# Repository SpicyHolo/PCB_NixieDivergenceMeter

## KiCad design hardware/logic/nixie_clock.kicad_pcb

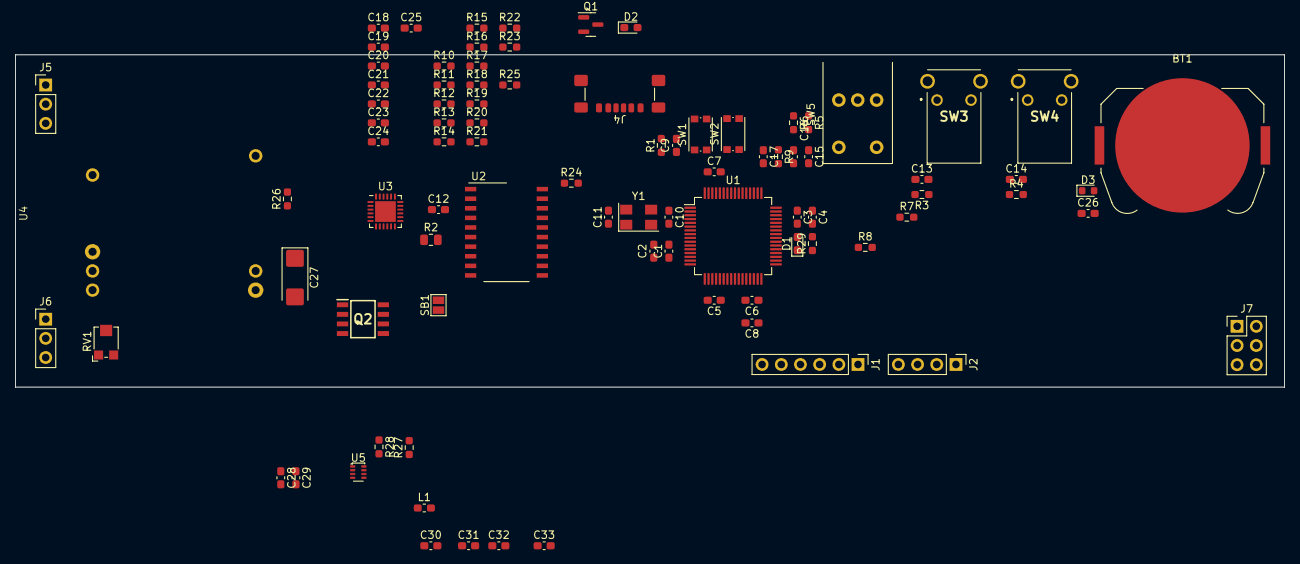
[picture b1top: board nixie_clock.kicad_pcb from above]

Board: 2 copper layers, 168.0 x 44.0 mm, 88 parts (0 on the bottom side), 56 nets.

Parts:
BT1: CR2032; BatteryHolder_Keystone_3034_1x20mm
C1: 10 nF; C_0603_1608Metric_Pad1.08x0.95mm_HandSolder
C2: 1 uF; C_0603_1608Metric_Pad1.08x0.95mm_HandSolder
C3, C5, C6, C7, C9, C12, C26: 100 nF; C_0603_1608Metric_Pad1.08x0.95mm_HandSolder
C4, C8: 4.7 uF; C_0603_1608Metric_Pad1.08x0.95mm_HandSolder
C10, C11: 10p; C_0603_1608Metric_Pad1.08x0.95mm_HandSolder
C13, C14, C17: 1u; C_0603_1608Metric_Pad1.08x0.95mm_HandSolder
C15, C16: 10n; C_0603_1608Metric_Pad1.08x0.95mm_HandSolder
C18, C22, C23, C25: 4u7; C_0603_1608Metric_Pad1.08x0.95mm_HandSolder
C19, C20, C21, C24, C29, C31: 100n; C_0603_1608Metric_Pad1.08x0.95mm_HandSolder
C27: 10uF; CP_EIA-6032-15_Kemet-U_Pad2.25x2.35mm_HandSolder
C28: 10u; C_0603_1608Metric_Pad1.08x0.95mm_HandSolder
C30: 33n; C_0603_1608Metric_Pad1.08x0.95mm_HandSolder
C32: 22p; C_0603_1608Metric_Pad1.08x0.95mm_HandSolder
C33: 100u; C_0603_1608Metric_Pad1.08x0.95mm_HandSolder
D1, D2: LED; LED_0603_1608Metric_Pad1.05x0.95mm_HandSolder
D3: BAT64-02V; D_0603_1608Metric
J1: Conn_01x06_Pin; PinHeader_1x06_P2.54mm_Vertical
J2: Conn_01x04; PinHeader_1x04_P2.54mm_Vertical
J4: USB_C_PD; USB_C_Receptacle_GCT_USB4135-GF-A_6P_TopMnt_Horizontal
J5, J6: Conn_01x03; PinHeader_1x03_P2.54mm_Vertical
J7: Conn_02x03_Odd_Even; PinHeader_2x03_P2.54mm_Vertical
L1: 5.6uH; L_0603_1608Metric_Pad1.05x0.95mm_HandSolder
Q1: 2N7002NXAKR; SOT-23
Q2: DMP3098LSD-13; SOIC127P600X175-8N
R1: 10K; R_0603_1608Metric_Pad0.98x0.95mm_HandSolder
R2: 10K; R_0805_2012Metric
R3, R4, R5, R6, R7, R8, R9, R28: 10k; R_0603_1608Metric_Pad0.98x0.95mm_HandSolder
R10, R11, R12, R13, R19, R20, R22, R23, R24, R29: 2k2; R_0603_1608Metric_Pad0.98x0.95mm_HandSolder
R14, R25: 20k; R_0603_1608Metric_Pad0.98x0.95mm_HandSolder
R15, R17: 5k1; R_0603_1608Metric_Pad0.98x0.95mm_HandSolder
R16, R18: 2k4; R_0603_1608Metric_Pad0.98x0.95mm_HandSolder
R21: DNP; R_0603_1608Metric_Pad0.98x0.95mm_HandSolder
R26: 100k; R_0603_1608Metric_Pad0.98x0.95mm_HandSolder
R27: 30k9; R_0603_1608Metric_Pad0.98x0.95mm_HandSolder
RV1: 100k; Potentiometer_Bourns_TC33X_Vertical
SB1: GS2; SolderJumper-2_P1.3mm_Open_Pad1.0x1.5mm
SW1: SW_RST; SW_Push_1P1T_NO_CK_KMR2
SW2: SW_BOOT; SW_Push_1P1T_NO_CK_KMR2
SW3, SW4: FSMRA4JH04
SW5: RotaryEncoder_Switch; RotaryEncoder_Bourns_Horizontal_PEC09-2xxxF-Sxxxx
U1: STM32F072RBTx; LQFP-64_10x10mm_P0.5mm
U2: DS3234; SO-20_12.8x7.5mm_P1.27mm
U3: CYPD3177-24LQXQ; QFN-24-1EP_4x4mm_P0.5mm_EP2.75x2.75mm
U4: 1364 HVPS; 1364 HVPS horizontal
U5: TPS62933FDRL; SOT-583-8
Y1: 8 MHz; Crystal_SMD_5032-4Pin_5.0x3.2mm

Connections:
+3.3V: C1.1, C2.1, C3.1, C4.1, C5.1, C6.1, C7.1, C8.1, C20.1, C21.1, C22.1, C32.1, C33.1, D2.2 (A), J1.1, J2.1, L1.2, R10.1, R11.1, R12.1, R15.1, R17.1, R19.1, R21.1, R27.1, U1.13 (VDDA), U1.19 (VDD), U1.32 (VDD), U1.48 (VDDIO2), U1.64 (VDD), U3.23 (VDDD)
+3V3: C12.1, J7.2, R2.2, R5.1, R6.1, SW2.2, SW3.2 (NO), SW4.2 (NO), SW5.S1, U2.4 (VCC)
+12V: C24.1, J7.1, Q2.5 (D2_1), Q2.6 (D2_2), U3.11 (VDC_OUT)
+BATT: C26.1, D3.1 (K), U1.1 (VBAT), U2.16 (VBAT)
+HV: J5.1, J5.2, J5.3, U4.1 (Vout)
/nixie_clock-MCU/BLANK: J7.3, U1.41 (PA8)
/nixie_clock-MCU/BOOT0: R1.2, SW2.1, U1.60 (BOOT0)
/nixie_clock-MCU/DEV_LED_K: D1.1 (K), R29.1
/nixie_clock-MCU/ENC_A: C15.1, R7.1, U1.14 (PA0)
/nixie_clock-MCU/ENC_B: C16.1, R8.1, U1.15 (PA1)
/nixie_clock-MCU/ENC_SW: C17.1, R9.1, SW5.S2, U1.16 (PA2)
/nixie_clock-MCU/HSE_IN: C10.1, U1.5 (PF0), Y1.3
/nixie_clock-MCU/HSE_OUT: C11.1, U1.6 (PF1), Y1.1
/nixie_clock-MCU/HVPS_EN: R26.2, U1.61 (PB8), U4.7 (Enable)
/nixie_clock-MCU/I2C1_SCL: R11.2, U1.58 (PB6), U3.13 (HPI_SCL)
/nixie_clock-MCU/I2C1_SDA: R12.2, U1.59 (PB7), U3.12 (HPI_SDA)
/nixie_clock-MCU/PD_FLIP: R10.2, U1.57 (PB5), U3.10 (FLIP)
/nixie_clock-MCU/RXD: J2.4, U1.42 (PA9)
/nixie_clock-MCU/SP1_NSS_DISP: J7.5, U1.51 (PC10)
/nixie_clock-MCU/SP1_NSS_RTC: U1.52 (PC11), U2.1 (~CS)
/nixie_clock-MCU/SP1_SCK: J7.6, U1.21 (PA5), U2.18 (SCK), U2.20 (SCK)
/nixie_clock-MCU/SPI1_MISO: U1.22 (PA6), U2.19 (DOUT)
/nixie_clock-MCU/SPI1_MOSI: J7.4, U1.23 (PA7), U2.17 (DIN)
/nixie_clock-MCU/SQW_IN: R2.1, U1.2 (PC13), U2.5 (~INT/SQW)
/nixie_clock-MCU/SW1: C13.1, R3.2, SW3.1 (COM), U1.17 (PA3)
/nixie_clock-MCU/SW2: C14.1, R4.2, SW4.1 (COM), U1.20 (PA4)
/nixie_clock-MCU/SWCLK: J1.2, U1.49 (PA14)
/nixie_clock-MCU/SWDIO: J1.4, U1.46 (PA13)
/nixie_clock-MCU/SW_RST: C9.1, J1.5, SB1.1 (G1), SW1.2, U1.7 (NRST)
/nixie_clock-MCU/TXD: J2.3, U1.43 (PA10)
/nixie_clock-PSU/FET_FAULT_D: Q1.3 (D), R13.2
/nixie_clock-PSU/LED_FAULT_K: D2.1 (K), R13.1
/nixie_clock-PSU/PDC_VCCD: C23.1, U3.24 (VCCD)
/nixie_clock-PSU/VBUS_FET_EN: R23.2, U3.3 (VBUS_FET_EN)
/nixie_clock-PSU/VBUS_FET_EN_R: C24.2, C25.2, R23.1, R24.2, R25.1
/nixie_clock-PSU/VBUS_FET_G: Q2.1 (S1), Q2.2 (G1), Q2.3 (S2), Q2.4 (G2), R24.1
GND: BT1.2 (-), C1.2, C2.2, C3.2, C4.2, C5.2, C6.2, C7.2, C8.2, C9.2, C10.2, C11.2, C12.2, C13.2, C14.2, C15.2, C16.2, C17.2, C18.2, C19.2, C20.2, C21.2, C22.2, C23.2, C26.2, C27.2, C28.2, C29.2, C30.2, C33.2, J1.3, J2.2, J4.A12 (GND), J4.B12 (GND), J4.S1 (SHIELD), J6.1, J6.2, J6.3, Q1.2 (S), R1.1, R3.1, R4.1, R9.2, R14.1, R16.2, R18.2, R20.2, R22.2, R26.1, R28.2, R29.2, RV1.3, SW1.1, SW3.3 (MH1), SW3.4 (MH2), SW4.3 (MH1), SW4.4 (MH2), SW5.C, U1.12 (VSSA), U1.18 (VSS), U1.31 (VSS), U1.47 (VSS), U1.63 (VSS), U2.2 (NC(CTG)), U2.7 (NC(CTG)), U2.8 (NC(CTG)), U2.9 (NC(CTG)), U2.10 (NC(CTG)), U2.11 (NC(CTG)), U2.12 (NC(CTG)), U2.13 (NC(CTG)), U2.14 (NC(CTG)), U2.15 (GND), U3.19 (GND), U3.22 (GND), U3.25 (GND), U4.3 (Gnd), U4.5 (Gnd), U5.4 (GND), Y1.2, Y1.4
unnamed: BT1.1 (+), D3.2 (A)
unnamed: D1.2 (A), U1.44 (PA11)
unnamed: J4.A5 (CC1), U3.15 (CC1)
unnamed: J4.B5 (CC2), U3.14 (CC2)
unnamed: Q1.1 (G), R14.2, U3.9 (FAULT)
unnamed: R5.2, R8.2, SW5.B
unnamed: R6.2, R7.2, SW5.A
unnamed: SB1.2 (G2), U2.6 (~RST)
unnamed: R19.2, R20.1, U3.5 (ISNK_COARSE)
unnamed: R21.2, R22.1, U3.6 (ISNK_FINE)
unnamed: R15.2, R16.1, U3.2 (VBUS_MAX)
unnamed: R17.2, R18.1, U3.1 (VBUS_MIN)
unnamed: RV1.2, U4.2 (Radj)
unnamed: C27.1, U4.4 (Vin)
unnamed: C31.1, U5.6 (BST)
unnamed: C32.2, R27.2, R28.1, U5.8 (FB)
unnamed: C30.1, U5.7 (SS)
unnamed: C31.2, L1.1, U5.5 (SW)
VBUS: C18.1, C19.1, C25.1, C28.1, C29.1, J4.A9 (VBUS), J4.B9 (VBUS), Q2.7 (D1_1), Q2.8 (D1_2), R25.2, U3.18 (VBUS_IN), U5.3 (VIN)

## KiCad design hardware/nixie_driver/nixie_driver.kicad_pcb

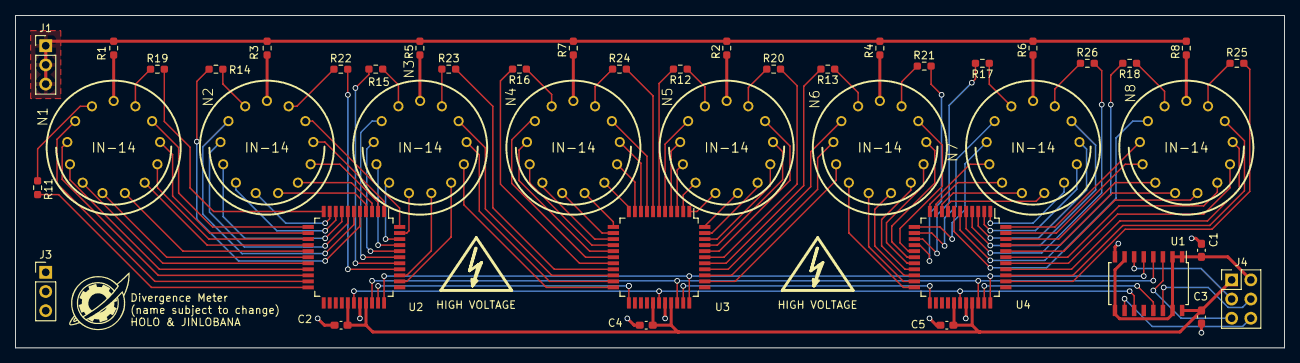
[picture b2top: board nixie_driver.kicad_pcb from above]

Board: 2 copper layers, 168.0 x 44.0 mm, 45 parts (0 on the bottom side), 134 nets.

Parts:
C1, C2, C3, C4, C5: 100nF; C_0603_1608Metric_Pad1.08x0.95mm_HandSolder
IMG1: LOGO; future_gadget_lab_neg_tiny
J1, J3: Conn_01x03; PinHeader_1x03_P2.54mm_Vertical
J4: Conn_02x03_Odd_Even; PinHeader_2x03_P2.54mm_Vertical
N1, N2, N3, N4, N5, N6, N7, N8: IN-14; nixies-us-IN-14
R1, R2, R3, R4, R5, R6, R7, R8: 10k; R_0603_1608Metric_Pad0.98x0.95mm_HandSolder
R11, R12, R13, R14, R15, R16, R17, R18, R19, R20, R21, R22, R23, R24, R25, R26: 73k; R_0603_1608Metric_Pad0.98x0.95mm_HandSolder
U1: CD40109B; SOIC-16W_5.3x10.2mm_P1.27mm
U2, U3, U4: TubeClock_HV5622; PQFP-44_10x10mm_P0.8mm

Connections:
+3.3V: C1.1, J4.2, U1.1 (VCC), U1.2 (ENABLE_A), U1.7 (ENABLE_B), U1.9 (ENABLE_C), U1.15 (ENABLE_D)
+12V: C2.1, C3.1, C4.1, C5.1, J4.1, U1.16 (VDD), U2.27 (~POL), U2.30 (VDD), U3.27 (~POL), U3.30 (VDD), U4.27 (~POL), U4.30 (VDD)
+HV: J1.1, J1.2, J1.3, R1.2, R2.2, R3.2, R4.2, R5.2, R6.2, R7.2, R8.2
/CLK: U1.11 (OUTPUT_C), U2.28 (CLK), U3.28 (CLK), U4.28 (CLK)
/CLK_{3.3V}: J4.6, U1.10 (INPUT_C)
/D_{IN}: U1.13 (OUTPUT_D), U4.32 (DATA_IN)
/D_{IN}_{3.3V}: J4.4, U1.14 (INPUT_D)
/D_{OUT1}: U3.32 (DATA_IN), U4.23 (DATA_OUT)
/D_{OUT2}: U2.32 (DATA_IN), U3.23 (DATA_OUT)
/NX1_K0: N1.0, U2.12 (HVOUT11)
/NX1_K1: N1.1, U2.21 (HVOUT2)
/NX1_K2: N1.2, U2.20 (HVOUT3)
/NX1_K3: N1.3, U2.19 (HVOUT4)
/NX1_K4: N1.4, U2.18 (HVOUT5)
/NX1_K5: N1.5, U2.17 (HVOUT6)
/NX1_K6: N1.6, U2.16 (HVOUT7)
/NX1_K7: N1.7, U2.15 (HVOUT8)
/NX1_K8: N1.8, U2.14 (HVOUT9)
/NX1_K9: N1.9, U2.13 (HVOUT10)
/NX1_LP: R11.2, U2.22 (HVOUT1)
/NX1_RP: R19.2, U2.11 (HVOUT12)
/NX2_K0: N2.0, U2.44 (HVOUT23)
/NX2_K1: N2.1, U2.6 (HVOUT17)
/NX2_K2: N2.2, U2.7 (HVOUT16)
/NX2_K3: N2.3, U2.8 (HVOUT15)
/NX2_K4: N2.4, U2.9 (HVOUT14)
/NX2_K5: N2.5, U2.10 (HVOUT13)
/NX2_K6: N2.6, U2.4 (HVOUT19)
/NX2_K7: N2.7, U2.3 (HVOUT20)
/NX2_K8: N2.8, U2.2 (HVOUT21)
/NX2_K9: N2.9, U2.1 (HVOUT22)
/NX2_LP: R14.2, U2.5 (HVOUT18)
/NX2_RP: R22.2, U2.37 (HVOUT30)
/NX3_K0: N3.0, U3.20 (HVOUT3)
/NX3_K1: N3.1, U2.39 (HVOUT28)
/NX3_K2: N3.2, U2.40 (HVOUT27)
/NX3_K3: N3.3, U2.41 (HVOUT26)
/NX3_K4: N3.4, U2.42 (HVOUT25)
/NX3_K5: N3.5, U2.43 (HVOUT24)
/NX3_K6: N3.6, U2.36 (HVOUT31)
/NX3_K7: N3.7, U2.35 (HVOUT32)
/NX3_K8: N3.8, U3.22 (HVOUT1)
/NX3_K9: N3.9, U3.21 (HVOUT2)
/NX3_LP: R15.2, U2.38 (HVOUT29)
/NX3_RP: R23.2, U3.19 (HVOUT4)
/NX4_K0: N4.0, U3.8 (HVOUT15)
/NX4_K1: N4.1, U3.17 (HVOUT6)
/NX4_K2: N4.2, U3.16 (HVOUT7)
/NX4_K3: N4.3, U3.15 (HVOUT8)
/NX4_K4: N4.4, U3.14 (HVOUT9)
/NX4_K5: N4.5, U3.13 (HVOUT10)
/NX4_K6: N4.6, U3.12 (HVOUT11)
/NX4_K7: N4.7, U3.11 (HVOUT12)
/NX4_K8: N4.8, U3.10 (HVOUT13)
/NX4_K9: N4.9, U3.9 (HVOUT14)
/NX4_LP: R16.2, U3.18 (HVOUT5)
/NX4_RP: R24.2, U3.7 (HVOUT16)
/NX5_K0: N5.0, U3.40 (HVOUT27)
/NX5_K1: N5.1, U3.5 (HVOUT18)
/NX5_K2: N5.2, U3.4 (HVOUT19)
/NX5_K3: N5.3, U3.3 (HVOUT20)
/NX5_K4: N5.4, U3.2 (HVOUT21)
/NX5_K5: N5.5, U3.1 (HVOUT22)
/NX5_K6: N5.6, U3.44 (HVOUT23)
/NX5_K7: N5.7, U3.43 (HVOUT24)
/NX5_K8: N5.8, U3.42 (HVOUT25)
/NX5_K9: N5.9, U3.41 (HVOUT26)
/NX5_LP: R12.2, U3.6 (HVOUT17)
/NX5_RP: R20.2, U3.39 (HVOUT28)
/NX6_K0: N6.0, U4.16 (HVOUT7)
/NX6_K1: N6.1, U3.37 (HVOUT30)
/NX6_K2: N6.2, U3.36 (HVOUT31)
/NX6_K3: N6.3, U3.35 (HVOUT32)
/NX6_K4: N6.4, U4.22 (HVOUT1)
/NX6_K5: N6.5, U4.21 (HVOUT2)
/NX6_K6: N6.6, U4.20 (HVOUT3)
/NX6_K7: N6.7, U4.19 (HVOUT4)
/NX6_K8: N6.8, U4.18 (HVOUT5)
/NX6_K9: N6.9, U4.17 (HVOUT6)
/NX6_LP: R13.2, U3.38 (HVOUT29)
/NX6_RP: R21.2, U4.15 (HVOUT8)
/NX7_K0: N7.0, U4.4 (HVOUT19)
/NX7_K1: N7.1, U4.13 (HVOUT10)
/NX7_K2: N7.2, U4.12 (HVOUT11)
/NX7_K3: N7.3, U4.11 (HVOUT12)
/NX7_K4: N7.4, U4.10 (HVOUT13)
/NX7_K5: N7.5, U4.9 (HVOUT14)
/NX7_K6: N7.6, U4.8 (HVOUT15)
/NX7_K7: N7.7, U4.1 (HVOUT22)
/NX7_K8: N7.8, U4.2 (HVOUT21)
/NX7_K9: N7.9, U4.3 (HVOUT20)
/NX7_LP: R17.2, U4.14 (HVOUT9)
/NX7_RP: R26.2, U4.5 (HVOUT18)
/NX8_K0: N8.0, U4.36 (HVOUT31)
/NX8_K1: N8.1, U4.7 (HVOUT16)
/NX8_K2: N8.2, U4.44 (HVOUT23)
/NX8_K3: N8.3, U4.43 (HVOUT24)
/NX8_K4: N8.4, U4.42 (HVOUT25)
/NX8_K5: N8.5, U4.41 (HVOUT26)
/NX8_K6: N8.6, U4.40 (HVOUT27)
/NX8_K7: N8.7, U4.39 (HVOUT28)
/NX8_K8: N8.8, U4.38 (HVOUT29)
/NX8_K9: N8.9, U4.37 (HVOUT30)
/NX8_LP: R18.2, U4.6 (HVOUT17)
/NX8_RP: R25.2, U4.35 (HVOUT32)
/~BL: U1.5 (OUTPUT_B), U2.33 (~BL), U3.33 (~BL), U4.33 (~BL)
/~BL_{3.3V}: J4.3, U1.6 (INPUT_B)
/~LE: U1.4 (OUTPUT_A), U2.31 (~LE), U3.31 (~LE), U4.31 (~LE)
/~LE_{3.3V}: J4.5, U1.3 (INPUT_A)
GND: C1.2, C2.2, C3.2, C4.2, C5.2, J3.1, J3.2, J3.3, U1.8 (VSS), U2.29 (VSS), U3.29 (VSS), U4.29 (VSS)
unnamed: N1.A, R1.1
unnamed: N1.LHDP, R11.1
unnamed: N1.RHDP, R19.1
unnamed: N2.A, R3.1
unnamed: N2.LHDP, R14.1
unnamed: N2.RHDP, R22.1
unnamed: N3.A, R5.1
unnamed: N3.LHDP, R15.1
unnamed: N3.RHDP, R23.1
unnamed: N4.A, R7.1
unnamed: N4.LHDP, R16.1
unnamed: N4.RHDP, R24.1
unnamed: N5.A, R2.1
unnamed: N5.LHDP, R12.1
unnamed: N5.RHDP, R20.1
unnamed: N6.A, R4.1
unnamed: N6.LHDP, R13.1
unnamed: N6.RHDP, R21.1
unnamed: N7.A, R6.1
unnamed: N7.LHDP, R17.1
unnamed: N7.RHDP, R26.1
unnamed: N8.A, R8.1
unnamed: N8.LHDP, R18.1
unnamed: N8.RHDP, R25.1

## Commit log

2023-11-15 Init repo
2023-11-17 Re-init
2023-12-04 Rough version of Main and driver board
2023-12-04 Changed connectors to driver board, fixed oscillator connections
2023-12-04 Inital PCB placement
2023-12-30 PCB layout, traces for nixie_driver, 3 Nixies + logic
2023-12-30 Finish PCB design for nixie_driver
2024-01-01 Troubleshooting logic board design, begin component placement, fix positioning of board connectors
